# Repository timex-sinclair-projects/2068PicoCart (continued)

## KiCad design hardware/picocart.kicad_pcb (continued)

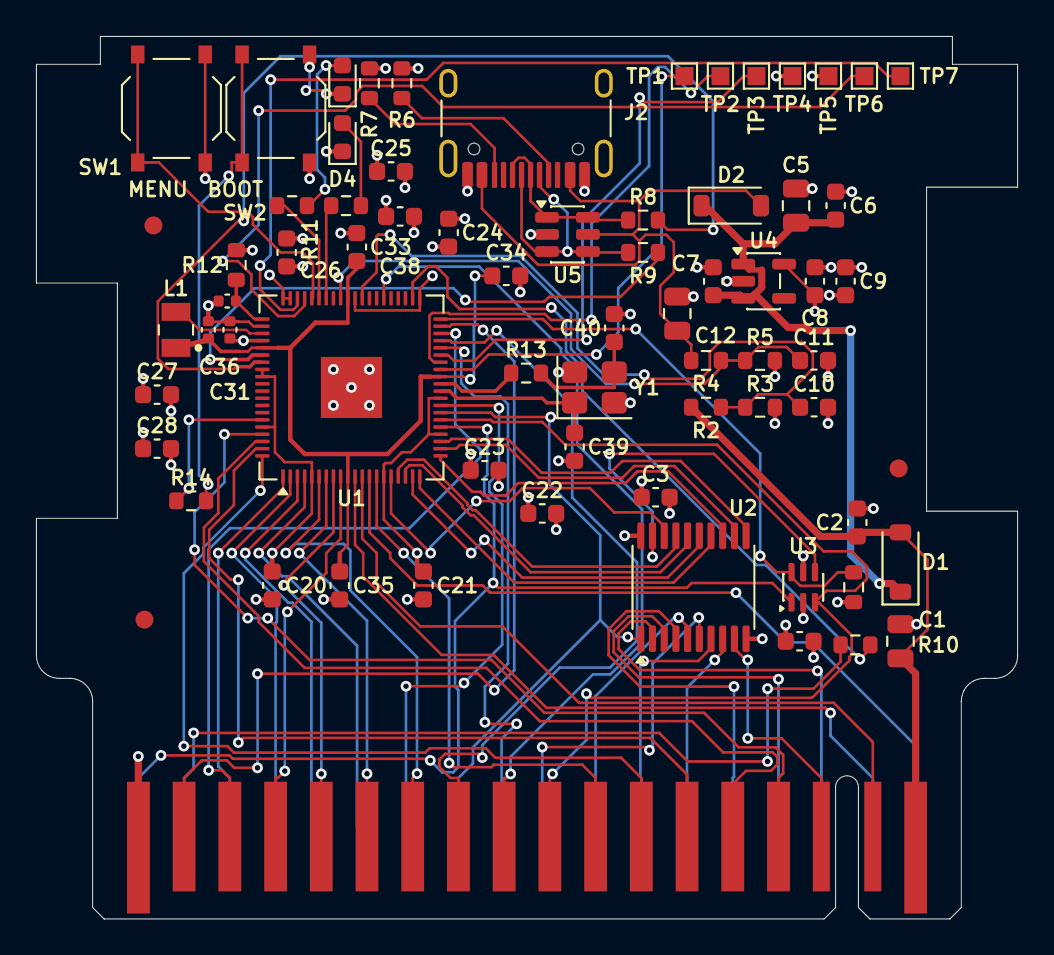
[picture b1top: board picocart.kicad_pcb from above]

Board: 4 copper layers, 54.5 x 49.0 mm, 70 parts (0 on the bottom side), 76 nets.

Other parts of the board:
FID1, FID2, FID3: Fiducial_1mm_Mask2mm

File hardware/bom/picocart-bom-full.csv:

"Value","Reference","Footprint","MPN","LCSC","Qty","Fitted by"
"10u","C1,C5,C12","Capacitor_SMD:C_0805_2012Metric","CL21A106KAYNNNE","C15850","3","JLCPCB"
"100n","C2-C4,C6,C10,C11,C20-C28,C33-C35","Capacitor_SMD:C_0603_1608Metric","CC0603KRX7R9BB104","C14663","18","JLCPCB"
"1u","C7,C9","Capacitor_SMD:C_0603_1608Metric","CL10A105KB8NNNC","C15849","2","JLCPCB"
"10u","C8,C38","Capacitor_SMD:C_0603_1608Metric","CL10A106KP8NNNC","C19702","2","JLCPCB"
"4.7u","C31,C32,C36","Capacitor_SMD:C_0402_1005Metric","CL05A475MP5NRNC","C23733","3","JLCPCB"
"18p","C39,C40","Capacitor_SMD:C_0603_1608Metric","CL10C180JB8NNNC","C1647","2","JLCPCB"
"B5819W","D1,D2","Diode_SMD:D_SOD-123","B5819W SL","C8598","2","JLCPCB"
"red","D3","LED_SMD:LED_0603_1608Metric","KT-0603R","C2286","1","JLCPCB"
"white","D4","LED_SMD:LED_0603_1608Metric","KT-0603W","C2290","1","JLCPCB"
"TS2068_Cart36","J1","picocart:TS2068_Cart36","","","1","none (board feature)"
"USB-C","J2","Connector_USB:USB_C_Receptacle_HRO_TYPE-C-31-M-12","HX TYPE-C 16PIN","C5178539","1","JLCPCB"
"3.3uH","L1","picocart:L_Abracon_AOTA-B201610","AOTA-B201610S3R3-101-T","C42411119","1","JLCPCB"
"10k","R1,R2,R4","Resistor_SMD:R_0603_1608Metric","0603WAF1002T5E","C25804","3","JLCPCB"
"15k","R3,R5","Resistor_SMD:R_0603_1608Metric","0603WAF1502T5E","C22809","2","JLCPCB"
"5k1","R6,R7","Resistor_SMD:R_0603_1608Metric","0603WAF5101T5E","C23186","2","JLCPCB"
"33","R8,R9,R12","Resistor_SMD:R_0603_1608Metric","0603WAF330JT5E","C23140","3","JLCPCB"
"0","R10","Resistor_SMD:R_0603_1608Metric","0603WAF0000T5E","C21189","1","hand (DNP)"
"1k","R11,R13,R14","Resistor_SMD:R_0603_1608Metric","0603WAF1001T5E","C21190","3","JLCPCB"
"3k3","R15","Resistor_SMD:R_0603_1608Metric","0603WAF3301T5E","C22978","1","JLCPCB"
"MENU","SW1","Button_Switch_SMD:SW_Push_1P1T_XKB_TS-1187A","TS-1187A-C-J-B","C318885","1","JLCPCB"
"BOOTSEL","SW2","Button_Switch_SMD:SW_Push_1P1T_XKB_TS-1187A","TS-1187A-C-J-B","C318885","1","JLCPCB"
"SWCLK","TP1","TestPoint:TestPoint_Pad_1.0x1.0mm","","","1","none (board feature)"
"SWDIO","TP2","TestPoint:TestPoint_Pad_1.0x1.0mm","","","1","none (board feature)"
"RUN","TP3","TestPoint:TestPoint_Pad_1.0x1.0mm","","","1","none (board feature)"
"+3V3","TP4","TestPoint:TestPoint_Pad_1.0x1.0mm","","","1","none (board feature)"
"GND","TP5","TestPoint:TestPoint_Pad_1.0x1.0mm","","","1","none (board feature)"
"UART_TX","TP6","TestPoint:TestPoint_Pad_1.0x1.0mm","","","1","none (board feature)"
"UART_RX","TP7","TestPoint:TestPoint_Pad_1.0x1.0mm","","","1","none (board feature)"
"RP2354B","U1","Package_DFN_QFN:QFN-80-1EP_10x10mm_P0.4mm_EP3.4x3.4mm","RP2354B","C39843328","1","JLCPCB"
"74LVC245APW","U2","Package_SO:TSSOP-20_4.4x6.5mm_P0.65mm","74LVC245APW,118","C6082","1","JLCPCB"
"74LVC1G332","U3","Package_TO_SOT_SMD:SOT-363_SC-70-6","74LVC1G332GW,125","C548342","1","JLCPCB"
"AP2112K-3.3","U4","Package_TO_SOT_SMD:SOT-23-5","AP2112K-3.3TRG1","C51118","1","JLCPCB"
"USBLC6-2SC6","U5","Package_TO_SOT_SMD:SOT-23-6","USBLC6-2SC6","C7519","1","JLCPCB"
"12MHz","Y1","Crystal:Crystal_SMD_3225-4Pin_3.2x2.5mm","X322512MOB4SI","C70565","1","JLCPCB"

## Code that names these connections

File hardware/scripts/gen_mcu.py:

#!/usr/bin/env python3
"""mcu.kicad_sch: RP2354B core, after tspico-hardware v3 (proven on proto1-3).

  U1  RP2354B (RP2350B symbol: same QFN-80 pinout; 2 MB flash in package, so the QSPI data
      and clock pins are left open and QSPI_SS only carries BOOTSEL)
  L1, C31, C36: core regulator (design guide fig. 4); R12/C32 VREG_AVDD filter
  C33-C35 DVDD 100n; C20-C28 one 100n per 3.3 V supply pin or pair
  Y1 12 MHz (CL 12 pF), C39/C40 18p, R13 1k in series with XOUT
  R14 1k QSPI_SS -> BOOTSEL; SW2 BOOTSEL button to GND; SWD, RUN and UART test pads
GPIO map: ../SCHEMATIC.md sheet 3. Only GPIO0-39 are 5 V tolerant: every dock signal is on 0-39.
"""
import os
import sys

sys.path.insert(0, os.path.dirname(os.path.abspath(__file__)))
from schlib import Sheet  # noqa: E402

R0603 = "Resistor_SMD:R_0603_1608Metric"
C0603 = "Capacitor_SMD:C_0603_1608Metric"
C0402 = "Capacitor_SMD:C_0402_1005Metric"
L_FP = "picocart:L_Abracon_AOTA-B201610"
TP_FP = "TestPoint:TestPoint_Pad_1.0x1.0mm"
OUT, IN, BI = "output", "input", "bidirectional"

GPIO = {
    **{i: (f"A{i}", IN) for i in range(16)},
    **{16 + i: (f"MD{i}", BI) for i in range(8)},
    24: ("ROSCS_n", IN), 25: ("MREQ_n", IN), 26: ("RD_n", IN), 27: ("WR_n", IN),
    28: ("IORQ_n", IN), 29: ("M1_n", IN), 30: ("RFSH_n", IN), 31: ("EXROM", IN),
    32: ("BUS_OFF", IN), 33: ("BE_GPIO", BI), 37: ("A7R", IN),
    40: ("DOCK_SENSE", IN), 41: ("VBUS_SENSE", IN),
    # 3.3 V-only controls on the top-left pins, under the buttons and LEDs (pins 54-56)
    43: ("LED2", OUT), 44: ("LED", OUT), 45: ("MENU_n", IN),
}
LOCAL = {46: "UART_TX", 47: "UART_RX"}
SPARE = [34, 35, 36, 38, 39, 42]  # 34/35 were I2C for an OLED (dropped: the dock hides it); 38/39 (pins 47/48) sit under the DOCK_SENSE pre-route: keep them spare


def main():
    s = Sheet("picocart.kicad_sch", "mcu.kicad_sch", "2068 PicoCart: RP2354B Core")
    s.text("RP2354B core per 'Hardware design with RP2350' (as tspico-hardware v3). GPIO map: ../SCHEMATIC.md sheet 3.", 20, 280, 2.2)
    s.text("GPIO40-47 are NOT 5 V tolerant: only the ADC sense dividers (<= 3.0 V) use them. GPIO43-45 drive only the LEDs/MENU (3.3 V). Spare: GPIO34, 35, 36, 38, 39, 42.", 20, 285, 2.0)
    s.power("+3V3", 300, 30, "#PWR03", flag=False)
    s.power("GND", 330, 40, "#PWR04", flag=False)

    U = s.place("MCU_RaspberryPi:RP2350B", "U1", "RP2354B", "Package_DFN_QFN:QFN-80-1EP_10x10mm_P0.4mm_EP3.4x3.4mm", 130, 150)
    names = U.names()
    by_name = {}
    for num, nm in names.items():
        by_name.setdefault(nm.split("/")[0], num)
    for g, (net, shape) in GPIO.items():
        s.glabel(net, U.pin(by_name[f"GPIO{g}"]), shape)
    for g, net in LOCAL.items():
        s.label(net, U.pin(by_name[f"GPIO{g}"]))
    for g in SPARE:
        s.nc(U.pin(by_name[f"GPIO{g}"]))
    for num, nm in names.items():
        if nm in ("IOVDD", "QSPI_IOVDD", "USB_OTP_VDD", "ADC_AVDD", "VREG_VIN"):
            s.label("+3V3", U.pin(num))
        elif nm == "VREG_AVDD":
            s.label("VREG_AVDD", U.pin(num))
        elif nm in ("GND", "VREG_PGND"):
            s.label("GND", U.pin(num))
        elif nm == "DVDD":
            s.label("DVDD", U.pin(num))
    s.label("VREG_LX", U.pin(by_name["VREG_LX"]))
    s.label("DVDD", U.pin(by_name["VREG_FB"]))
    s.label("XIN", U.pin(by_name["XIN"])); s.label("XOUT", U.pin(by_name["XOUT"]))
    s.label("SWCLK", U.pin(by_name["SWCLK"])); s.label("SWDIO", U.pin(by_name["SWDIO"]))
    s.label("RUN", U.pin(by_name["RUN"]))
    s.glabel("USB_DM", U.pin(by_name["USB_DM"]), BI); s.glabel("USB_DP", U.pin(by_name["USB_DP"]), BI)
    for nm in ("QSPI_SD0", "QSPI_SD1", "QSPI_SD2", "QSPI_SD3", "QSPI_SCLK"):
        s.nc(U.pin(by_name[nm]))          # bonded to the in-package flash: no copper
    s.label("nQSPI_SS", U.pin(by_name["~{QSPI_SS}"]))

    # ---- core regulator ---------------------------------------------------------------
    L1 = s.place("Device:L", "L1", "3.3uH", L_FP, 250, 60)
    s.label("VREG_LX", L1.pin("1")); s.label("DVDD", L1.pin("2"))     # dot = pad 2 = DVDD side
    for k, (ref, net, val, fp) in enumerate([("C36", "DVDD", "4.7u", C0402), ("C31", "+3V3", "4.7u", C0402),
                                             ("C33", "DVDD", "100n", C0603), ("C34", "DVDD", "100n", C0603), ("C35", "DVDD", "100n", C0603)]):
        C = s.place("Device:C", ref, val, fp, 265 + 10 * k, 60)
        s.label(net, C.pin("1")); s.label("GND", C.pin("2"))
    s.text("L1 Abracon AOTA-B201610S3R3-101-T (polarised: dot = pad 2 = DVDD). C36 COUT, C31 CIN at VREG_VIN. C33-C35 at DVDD pins 51, 32, 10.", 245, 75, 1.5)
    R12 = s.place("Device:R", "R12", "33", R0603, 300, 85)
    s.label("+3V3", R12.pin("1")); s.label("VREG_AVDD", R12.pin("2"))
    C32 = s.place("Device:C", "C32", "4.7u", C0402, 315, 85)
    s.label("VREG_AVDD", C32.pin("1")); s.label("GND", C32.pin("2"))
    FL2 = s.place("power:PWR_FLAG", "#FLG02", "PWR_FLAG", "", 330, 85)
    s.label("VREG_AVDD", FL2.pin("1"))
    FL = s.place("power:PWR_FLAG", "#FLG03", "PWR_FLAG", "", 300, 60)
    s.label("DVDD", FL.pin("1"))

    # ---- 3.3 V decoupling: 9 x 100 nF --------------------------------------------------
    for k in range(9):
        C = s.place("Device:C", f"C{20 + k}", "100n", C0603, 250 + 9 * k, 100)
        s.label("+3V3", C.pin("1")); s.label("GND", C.pin("2"))
    s.text("C20-C28: one per 3.3 V supply pin or adjacent pair (5, 15, 24, 29, 41, 50, 59/60, 68/69, 76); pin 64 has C31.", 245, 115, 1.5)
    C38 = s.place("Device:C", "C38", "10u", C0603, 340, 100)
    s.label("+3V3", C38.pin("1")); s.label("GND", C38.pin("2"))

    # ---- crystal ----------------------------------------------------------------------
    Y1 = s.place("Device:Crystal_GND24", "Y1", "12MHz", "Crystal:Crystal_SMD_3225-4Pin_3.2x2.5mm", 270, 150)
    s.label("XIN", Y1.pin("1")); s.label("XOUT_R", Y1.pin("3")); s.label("GND", Y1.pin("2")); s.label("GND", Y1.pin("4"))
    R13 = s.place("Device:R", "R13", "1k", R0603, 295, 150)
    s.label("XOUT", R13.pin("1")); s.label("XOUT_R", R13.pin("2"))
    C39 = s.place("Device:C", "C39", "18p", C0603, 255, 165)
    s.label("XIN", C39.pin("1")); s.label("GND", C39.pin("2"))
    C40 = s.place("Device:C", "C40", "18p", C0603, 285, 165)
    s.label("XOUT_R", C40.pin("1")); s.label("GND", C40.pin("2"))
    s.text("Y1 YXC X322512MOB4SI 12 MHz CL 12 pF: C39/C40 18 pF (~3 pF stray). R13 1 k in series with XOUT.", 245, 180, 1.5)

    # ---- BOOTSEL, debug, UART -----------------------------------------------------------
    R14 = s.place("Device:R", "R14", "1k", R0603, 250, 210)
    s.label("nQSPI_SS", R14.pin("1")); s.label("BOOTSEL", R14.pin("2"))
    SW2 = s.place("Switch:SW_Push", "SW2", "BOOTSEL", "Button_Switch_SMD:SW_Push_1P1T_XKB_TS-1187A", 250, 195)
    s.label("BOOTSEL", SW2.pin("1")); s.label("GND", SW2.pin("2"))
    pads = [("TP1", "SWCLK"), ("TP2", "SWDIO"), ("TP3", "RUN"), ("TP4", "+3V3"), ("TP5", "GND"),
            ("TP6", "UART_TX"), ("TP7", "UART_RX")]
    for k, (ref, net) in enumerate(pads):
        T = s.place("Connector:TestPoint", ref, net, TP_FP, 270 + 12 * k, 230)
        s.label(net, T.pin("1"))
    s.text("TP1-TP5 SWD/RUN/power, TP6/TP7 UART. SW2 BOOTSEL: hold while plugging in USB (or while pulsing RUN) for the ROM bootloader. RUN has the chip's internal pull-up.", 245, 245, 1.5)

    s.write()
    print("wrote mcu.kicad_sch")


if __name__ == "__main__":
    main()

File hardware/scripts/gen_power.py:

#!/usr/bin/env python3
"""power.kicad_sch: power input, 3V3 regulator, sense dividers, USB-C, MENU button, LED.

  D1/D2  B5819W diode-OR: DOCK_5V and VBUS -> +5V (5V_INT). Neither source back-feeds the other.
  U4     AP2112K-3.3, C5-C9
  R2/R3, R4/R5  10k/15k dividers -> DOCK_SENSE, VBUS_SENSE (ADC0/ADC1, 3.0 V at 5 V)
  J2     USB-C C5178539 (HRO TYPE-C-31-M-12 land pattern), R6/R7 5k1 Rd, U5 USBLC6-2SC6,
         R8/R9 33R series (as tspico v3: JLC basic; Raspberry Pi suggests 27R)
  SW1    MENU, D3/R11 and D4/R15 status LEDs
"""
import os
import sys

sys.path.insert(0, os.path.dirname(os.path.abspath(__file__)))
from schlib import Sheet  # noqa: E402

R0603 = "Resistor_SMD:R_0603_1608Metric"
C0603 = "Capacitor_SMD:C_0603_1608Metric"
C0805 = "Capacitor_SMD:C_0805_2012Metric"
OUT, IN, BI = "output", "input", "bidirectional"


def rc(s, kind, ref, val, fp, x, y, a, b, ga=False, gb=False):
    P = s.place("Device:" + kind, ref, val, fp, x, y)
    (s.glabel if ga else s.label)(a, P.pin("1"), *([BI] if ga else []))
    (s.glabel if gb else s.label)(b, P.pin("2"), *([BI] if gb else []))
    return P


def main():
    s = Sheet("picocart.kicad_sch", "power.kicad_sch", "2068 PicoCart: Power, USB, Controls")
    s.text("Power: dock +5V and USB VBUS diode-ORed into +5V (5V_INT), AP2112K-3.3. The firmware keeps BUS_OFF high unless DOCK_SENSE shows the 2068 is on.", 20, 280, 2.0)
    s.power("+3V3", 250, 30, "#PWR05", flag=False)
    s.power("+5V", 280, 30, "#PWR06", flag=True)
    s.power("GND", 310, 30, "#PWR07", flag=False)

    # ---- diode-OR, regulator --------------------------------------------------------------
    D1 = s.place("Device:D_Schottky", "D1", "B5819W", "Diode_SMD:D_SOD-123", 60, 50)
    s.label("+5V", D1.pin("1")); s.glabel("DOCK_5V", D1.pin("2"), IN)
    D2 = s.place("Device:D_Schottky", "D2", "B5819W", "Diode_SMD:D_SOD-123", 60, 70)
    s.label("+5V", D2.pin("1")); s.label("VBUS", D2.pin("2"))
    rc(s, "C", "C5", "10u", C0805, 90, 50, "+5V", "GND")
    rc(s, "C", "C6", "100n", C0603, 100, 50, "+5V", "GND")
    U4 = s.place("Regulator_Linear:AP2112K-3.3", "U4", "AP2112K-3.3", "Package_TO_SOT_SMD:SOT-23-5", 140, 60)
    s.label("+5V", U4.pin("VIN")); s.label("+5V", U4.pin("EN")); s.label("GND", U4.pin("GND"))
    s.label("+3V3", U4.pin("VOUT")); s.nc(U4.pin("NC"))
    rc(s, "C", "C7", "1u", C0603, 115, 75, "+5V", "GND")
    rc(s, "C", "C8", "10u", C0603, 170, 75, "+3V3", "GND")
    rc(s, "C", "C9", "1u", C0603, 180, 75, "+3V3", "GND")

    # ---- sense dividers -------------------------------------------------------------------
    rc(s, "R", "R2", "10k", R0603, 60, 110, "DOCK_5V", "DOCK_SENSE", ga=True, gb=True)
    rc(s, "R", "R3", "15k", R0603, 75, 110, "DOCK_SENSE", "GND", ga=True)
    rc(s, "C", "C10", "100n", C0603, 90, 110, "DOCK_SENSE", "GND", ga=True)
    rc(s, "R", "R4", "10k", R0603, 60, 135, "VBUS", "VBUS_SENSE", gb=True)
    rc(s, "R", "R5", "15k", R0603, 75, 135, "VBUS_SENSE", "GND", ga=True)
    rc(s, "C", "C11", "100n", C0603, 90, 135, "VBUS_SENSE", "GND", ga=True)

    # ---- USB-C ----------------------------------------------------------------------------
    J2 = s.place("Connector:USB_C_Receptacle_USB2.0_16P", "J2", "USB-C", "Connector_USB:USB_C_Receptacle_HRO_TYPE-C-31-M-12", 220, 160)
    for pin in ("A4", "A9", "B4", "B9"):
        s.label("VBUS", J2.pin(pin))
    for pin in ("A8", "B8"):
        s.nc(J2.pin(pin))
    for pin in ("A1", "A12", "B1", "B12", "SH"):
        s.label("GND", J2.pin(pin))
    s.label("USB_DP_C", J2.pin("A6")); s.label("USB_DP_C", J2.pin("B6"))
    s.label("USB_DM_C", J2.pin("A7")); s.label("USB_DM_C", J2.pin("B7"))
    s.label("CC1", J2.pin("A5")); s.label("CC2", J2.pin("B5"))
    F = s.place("power:PWR_FLAG", "#FLG04", "PWR_FLAG", "", 260, 120)
    s.label("VBUS", F.pin("1"))
    rc(s, "R", "R6", "5k1", R0603, 270, 140, "CC1", "GND")
    rc(s, "R", "R7", "5k1", R0603, 285, 140, "CC2", "GND")
    rc(s, "R", "R8", "33", R0603, 270, 180, "USB_DP_C", "USB_DP", gb=True)
    rc(s, "R", "R9", "33", R0603, 285, 180, "USB_DM_C", "USB_DM", gb=True)
    rc(s, "C", "C12", "10u", C0805, 300, 140, "VBUS", "GND")
    U5 = s.place("Power_Protection:USBLC6-2SC6", "U5", "USBLC6-2SC6", "Package_TO_SOT_SMD:SOT-23-6", 320, 180)
    s.label("USB_DP_C", U5.pin("1")); s.label("USB_DP_C", U5.pin("6"))
    s.label("USB_DM_C", U5.pin("3")); s.label("USB_DM_C", U5.pin("4"))
    s.label("GND", U5.pin("2")); s.label("VBUS", U5.pin("5"))
    s.text("J2: USB 2.0 device. R6/R7 separate 5.1 k Rd per CC pin. U5 between J2 and R8/R9.", 200, 210, 1.5)

    # ---- MENU button, LED ------------------------------------------------------------------
    SW1 = s.place("Switch:SW_Push", "SW1", "MENU", "Button_Switch_SMD:SW_Push_1P1T_XKB_TS-1187A", 60, 200)
    s.glabel("MENU_n", SW1.pin("1"), OUT); s.label("GND", SW1.pin("2"))
    R11 = s.place("Device:R", "R11", "1k", R0603, 60, 230)
    s.glabel("LED", R11.pin("1"), IN); s.label("LED_A", R11.pin("2"))
    D3 = s.place("Device:LED", "D3", "red", "LED_SMD:LED_0603_1608Metric", 90, 230)
    s.label("GND", D3.pin("1")); s.label("LED_A", D3.pin("2"))
    R15 = s.place("Device:R", "R15", "3k3", R0603, 60, 260)   # white LED: 100 R was far too bright
    s.glabel("LED2", R15.pin("1"), IN); s.label("LED2_A", R15.pin("2"))
    D4 = s.place("Device:LED", "D4", "white", "LED_SMD:LED_0603_1608Metric", 90, 260)
    s.label("GND", D4.pin("1")); s.label("LED2_A", D4.pin("2"))
    s.text("SW1 MENU (internal pull-up on GPIO45): hold at power-on for the menu. D3 red LED on GPIO44, D4 white LED on GPIO43 (R15 3k3: a white LED is far brighter than the red one at the same current).", 30, 270, 1.5)


    s.write()
    print("wrote power.kicad_sch")


if __name__ == "__main__":
    main()

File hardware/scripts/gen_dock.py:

#!/usr/bin/env python3
"""dock.kicad_sch: the TS2068 dock fingers, the data-bus buffer and its enable gate.

  J1  TS2068_Cart36: every dock signal goes to the MCU sheet (BE through R10, DNP)
  U2  74LVC245 (3V3): A side = dock D0-D7, B side = MD0-MD7. DIR = /RD (read: B->A, the
      cart drives the bus), /OE = BUF_OE_n
  U3  74LVC1G332: BUF_OE_n = /ROSCS OR /MREQ OR BUS_OFF
  R1  10k pull-up on BUS_OFF: the bus stays released until the firmware is serving
"""
import os
import sys

sys.path.insert(0, os.path.dirname(os.path.abspath(__file__)))
from schlib import Sheet  # noqa: E402

R0603 = "Resistor_SMD:R_0603_1608Metric"
C0603 = "Capacitor_SMD:C_0603_1608Metric"
C0805 = "Capacitor_SMD:C_0805_2012Metric"
OUT, IN, BI = "output", "input", "bidirectional"

# dock pin -> (net, shape as seen from this sheet); None = local
J1_NETS = {
    1: "A14", 2: "DOCK_5V", 3: "A12", 4: "A13", 5: "D0", 6: "D7", 7: "D1", 8: "A0", 9: "D2", 10: "A1",
    11: "D6", 12: "A2", 13: "D5", 14: "A3", 15: "D3", 16: "A15", 17: "D4", 18: "MREQ_n", 19: "IORQ_n",
    20: "A7R", 21: "RD_n", 22: "M1_n", 23: "WR_n", 24: "A8", 25: "A7", 26: "A9", 27: "A6", 28: "A10",
    29: "A5", 30: "A11", 31: "A4", 32: "RFSH_n", 33: "BE", 34: "EXROM", 35: "ROSCS_n", 36: "GND",
}
LOCAL = {"D0", "D1", "D2", "D3", "D4", "D5", "D6", "D7", "BE", "GND"}


def main():
    s = Sheet("picocart.kicad_sch", "dock.kicad_sch", "2068 PicoCart: Dock Interface")
    s.text("Dock fingers: odd pins on the bottom side, even on the top (EasyEDA 2068-cart-SMD). A13B/A14B/A15B wired straight; firmware can invert.", 20, 270, 2.0)
    s.text("U2 only drives the dock during a dock-selected memory cycle (/ROSCS and /MREQ low) and only after the firmware pulls BUS_OFF low.", 20, 275, 2.0)
    s.power("+3V3", 250, 30, "#PWR01", flag=False)
    s.power("GND", 280, 30, "#PWR02", flag=True)

    J1 = s.place("picocart:TS2068_Cart36", "J1", "TS2068_Cart36", "picocart:TS2068_Cart36", 80, 140)
    for pin, net in J1_NETS.items():
        if net in LOCAL:
            s.label(net, J1.pin(str(pin)))
        elif net == "DOCK_5V":
            s.glabel(net, J1.pin(str(pin)), OUT)
        else:
            s.glabel(net, J1.pin(str(pin)), IN)
    F = s.place("power:PWR_FLAG", "#FLG01", "PWR_FLAG", "", 40, 60)
    s.glabel("DOCK_5V", F.pin("1"), OUT)
    C1 = s.place("Device:C", "C1", "10u", C0805, 40, 80)
    s.glabel("DOCK_5V", C1.pin("1"), OUT); s.label("GND", C1.pin("2"))
    C2 = s.place("Device:C", "C2", "100n", C0603, 55, 80)
    s.glabel("DOCK_5V", C2.pin("1"), OUT); s.label("GND", C2.pin("2"))
    R10 = s.place("Device:R", "R10", "0", R0603, 40, 230, dnp=True)
    s.label("BE", R10.pin("1")); s.glabel("BE_GPIO", R10.pin("2"), BI)
    s.text("C1/C2 at finger 2. R10 (DNP) connects BE to GPIO33 only if wanted.", 20, 250, 1.5)

    # ---- U2 74LVC245: pin 1 DIR, 2-9 A0-A7, 10 GND, 11-18 B7-B0, 19 /OE, 20 VCC ------------
    U2 = s.place("74xx:74LS245", "U2", "74LVC245APW", "Package_SO:TSSOP-20_4.4x6.5mm_P0.65mm", 200, 140)
    s.glabel("RD_n", U2.pin("1"), IN)
    for k in range(8):
        s.label(f"D{k}", U2.pin(str(2 + k)))
        s.glabel(f"MD{k}", U2.pin(str(18 - k)), BI)
    s.label("GND", U2.pin("10"))
    s.label("BUF_OE_n", U2.pin("19"))
    s.label("+3V3", U2.pin("20"))
    C3 = s.place("Device:C", "C3", "100n", C0603, 240, 120)
    s.label("+3V3", C3.pin("1")); s.label("GND", C3.pin("2"))

    # ---- U3 74LVC1G332: 1, 3, 6 inputs, 4 Y, 5 VCC, 2 GND --------------------------------
    U3 = s.place("74xGxx:74LVC1G332", "U3", "74LVC1G332", "Package_TO_SOT_SMD:SOT-363_SC-70-6", 200, 220)
    s.glabel("ROSCS_n", U3.pin("1"), IN)
    s.glabel("MREQ_n", U3.pin("3"), IN)
    s.glabel("BUS_OFF", U3.pin("6"), IN)
    s.label("BUF_OE_n", U3.pin("4"))
    s.label("+3V3", U3.pin("5")); s.label("GND", U3.pin("2"))
    C4 = s.place("Device:C", "C4", "100n", C0603, 240, 210)
    s.label("+3V3", C4.pin("1")); s.label("GND", C4.pin("2"))
    R1 = s.place("Device:R", "R1", "10k", R0603, 240, 235)
    s.label("+3V3", R1.pin("1")); s.glabel("BUS_OFF", R1.pin("2"), IN)
    s.text("BUF_OE_n = /ROSCS | /MREQ | BUS_OFF. R1 holds BUS_OFF high through reset, boot and USB-only power.", 170, 250, 1.5)

    s.write()
    print("wrote dock.kicad_sch")


if __name__ == "__main__":
    main()

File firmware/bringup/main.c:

// 2068 PicoCart bring-up firmware.
//
// Safe in or out of the 2068: BUS_OFF is driven high before anything else, so the
// 74LVC245 never drives the dock data bus, and every dock pin is an input.
//
// Once a second, over USB serial, it prints:
//   - VBUS and DOCK +5 V through their 10k/15k sense dividers (ADC1/ADC0)
//   - MENU, BUS_OFF and BE_GPIO levels
//   - edge counts on every dock control line and on A0-A15 over a 100 ms window
//     (all zero with the 2068 off; thousands with it running)
//   - an MD0-MD7 float test: with the buffer off, the pull-ups and pull-downs must win
// D3 (red) and D4 (white) blink alternately; holding MENU lights both.

#include <stdio.h>
#include "pico/stdlib.h"
#include "hardware/adc.h"
#include "hardware/clocks.h"
#include "hardware/gpio.h"

enum {
    PIN_MD0 = 16, PIN_ROSCS = 24, PIN_MREQ = 25, PIN_RD = 26, PIN_WR = 27, PIN_IORQ = 28,
    PIN_M1 = 29, PIN_RFSH = 30, PIN_EXROM = 31, PIN_BUS_OFF = 32, PIN_BE = 33,
    PIN_A7R = 37, PIN_DOCK_SENSE = 40, PIN_VBUS_SENSE = 41,
    PIN_LED2 = 43, PIN_LED = 44, PIN_MENU = 45,
};

static const struct { int pin; const char *name; } CTRL[] = {
    {PIN_ROSCS, "ROSCS"}, {PIN_MREQ, "MREQ"}, {PIN_RD, "RD"}, {PIN_WR, "WR"}, {PIN_IORQ, "IORQ"},
    {PIN_M1, "M1"}, {PIN_RFSH, "RFSH"}, {PIN_EXROM, "EXROM"}, {PIN_A7R, "A7R"}, {PIN_BE, "BE"},
};
#define NCTRL (sizeof CTRL / sizeof CTRL[0])

static float sense_volts(int adc_input) {
    adc_select_input(adc_input);
    uint32_t sum = 0;
    for (int i = 0; i < 16; i++) sum += adc_read();
    float v_adc = (sum / 16.0f) * 3.3f / 4095.0f;
    return v_adc * (10.0f + 15.0f) / 15.0f;          // undo the 10k/15k divider
}

static void input_pin(int pin) {
    gpio_init(pin);
    gpio_set_dir(pin, GPIO_IN);
    gpio_disable_pulls(pin);                          // dock pins: no pulls (RP2350-E9)
}


// MD0-7 float test: returns the byte read with pull-downs and with pull-ups.
static void md_float(uint8_t *lo, uint8_t *hi) {
    for (int i = 0; i < 8; i++) gpio_pull_down(PIN_MD0 + i);
    sleep_us(200);
    *lo = (gpio_get_all64() >> PIN_MD0) & 0xff;
    for (int i = 0; i < 8; i++) gpio_pull_up(PIN_MD0 + i);
    sleep_us(200);
    *hi = (gpio_get_all64() >> PIN_MD0) & 0xff;
    for (int i = 0; i < 8; i++) gpio_disable_pulls(PIN_MD0 + i);
}

int main(void) {
    // 1. keep the bus buffer off before anything else
    gpio_init(PIN_BUS_OFF);
    gpio_put(PIN_BUS_OFF, 1);
    gpio_set_dir(PIN_BUS_OFF, GPIO_OUT);

    // 2. every dock signal (A0-15, MD0-7, controls) is an input
    for (int p = 0; p <= 31; p++) input_pin(p);
    input_pin(PIN_BE);
    input_pin(PIN_A7R);

    gpio_init(PIN_MENU); gpio_set_dir(PIN_MENU, GPIO_IN); gpio_pull_up(PIN_MENU);
    gpio_init(PIN_LED); gpio_set_dir(PIN_LED, GPIO_OUT);
    gpio_init(PIN_LED2); gpio_set_dir(PIN_LED2, GPIO_OUT);

    adc_init();
    adc_gpio_init(PIN_DOCK_SENSE);                    // ADC0
    adc_gpio_init(PIN_VBUS_SENSE);                    // ADC1

    stdio_init_all();
    for (int i = 0; i < 30 && !stdio_usb_connected(); i++) sleep_ms(100);
    printf("\n2068 PicoCart bring-up, %lu MHz sys clock\n", (unsigned long)(clock_get_hz(clk_sys) / 1000000));

    uint32_t tick = 0;
    for (;;) {
        // 100 ms sampling window: count edges on the controls and on the address bus
        uint32_t edges[NCTRL] = {0}, addr_changes = 0, samples = 0;
        uint64_t prev = gpio_get_all64();
        absolute_time_t end = make_timeout_time_ms(100);
        while (!time_reached(end)) {
            uint64_t now = gpio_get_all64(), diff = now ^ prev;
            if (diff) {
                for (unsigned i = 0; i < NCTRL; i++) edges[i] += (diff >> CTRL[i].pin) & 1;
                addr_changes += (diff & 0xffff) != 0;
                prev = now;
            }
            samples++;
        }

        bool menu = !gpio_get(PIN_MENU);
        gpio_put(PIN_LED, menu || (tick & 1));
        gpio_put(PIN_LED2, menu || !(tick & 1));

        float vbus = sense_volts(1), dock = sense_volts(0);
        uint8_t md_lo, md_hi;
        md_float(&md_lo, &md_hi);

        printf("[%4lu] VBUS %.2f V  DOCK %.2f V  MENU %s  BUS_OFF %d  BE %d  MD float %s (pd %02x pu %02x)\n",
               (unsigned long)tick, vbus, dock, menu ? "DOWN" : "up", gpio_get(PIN_BUS_OFF), gpio_get(PIN_BE),
               (md_lo == 0x00 && md_hi == 0xff) ? "ok" : "DRIVEN?", md_lo, md_hi);
        printf("       edges/100ms:");
        for (unsigned i = 0; i < NCTRL; i++) printf(" %s %lu", CTRL[i].name, (unsigned long)edges[i]);
        printf("  addr %lu  (levels %08lx, %lu samples)\n", (unsigned long)addr_changes,
               (unsigned long)(prev & 0xffffffff), (unsigned long)samples);

        tick++;
        sleep_ms(900);
    }
}

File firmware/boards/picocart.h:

// Board header for the 2068 PicoCart (RP2354B: RP2350B die + 2 MB flash in the package).
// Pin map: hardware/scripts/gen_mcu.py and SCHEMATIC.md sheet 3.

#ifndef _BOARDS_PICOCART_H
#define _BOARDS_PICOCART_H

pico_board_cmake_set(PICO_PLATFORM, rp2350)

#define PICOCART_2068

// --- RP2350 VARIANT: QFN-80, 48 GPIO ---
#define PICO_RP2350A 0

// --- UART: test pads TP6/TP7, GPIO46/47 = UART0 TX/RX (the bring-up firmware uses USB stdio) ---
#ifndef PICO_DEFAULT_UART
#define PICO_DEFAULT_UART 0
#endif
#ifndef PICO_DEFAULT_UART_TX_PIN
#define PICO_DEFAULT_UART_TX_PIN 46
#endif
#ifndef PICO_DEFAULT_UART_RX_PIN
#define PICO_DEFAULT_UART_RX_PIN 47
#endif

// --- LEDs: D3 red on GPIO44 (default), D4 white on GPIO43 ---
#ifndef PICO_DEFAULT_LED_PIN
#define PICO_DEFAULT_LED_PIN 44
#endif

// --- FLASH: 2 MB in package ---
#define PICO_BOOT_STAGE2_CHOOSE_W25Q080 1
#ifndef PICO_FLASH_SPI_CLKDIV
#define PICO_FLASH_SPI_CLKDIV 2
#endif
pico_board_cmake_set_default(PICO_FLASH_SIZE_BYTES, (2 * 1024 * 1024))
#ifndef PICO_FLASH_SIZE_BYTES
#define PICO_FLASH_SIZE_BYTES (2 * 1024 * 1024)
#endif

// --- CRYSTAL: 12 MHz YXC X322512MOB4SI; allow a slow start ---
#ifndef PICO_XOSC_STARTUP_DELAY_MULTIPLIER
#define PICO_XOSC_STARTUP_DELAY_MULTIPLIER 64
#endif

// No SMPS mode pin, VBUS pin or VSYS pin: GPIO23-29 are dock signals on this board.

pico_board_cmake_set_default(PICO_RP2350_A2_SUPPORTED, 1)
#ifndef PICO_RP2350_A2_SUPPORTED
#define PICO_RP2350_A2_SUPPORTED 1
#endif

#endif
